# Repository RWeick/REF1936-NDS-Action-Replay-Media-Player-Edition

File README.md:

# REF1936-NDS-Action-Replay-Media-Player-Edition
The flash dump, schematic, and gerbers for the Datel Nintendo DS Action Replay Media Player edition. This is the version of the NDS Action Replay that has a functional micro SD card slot on it.

PCB Thickness: 0.8 mm

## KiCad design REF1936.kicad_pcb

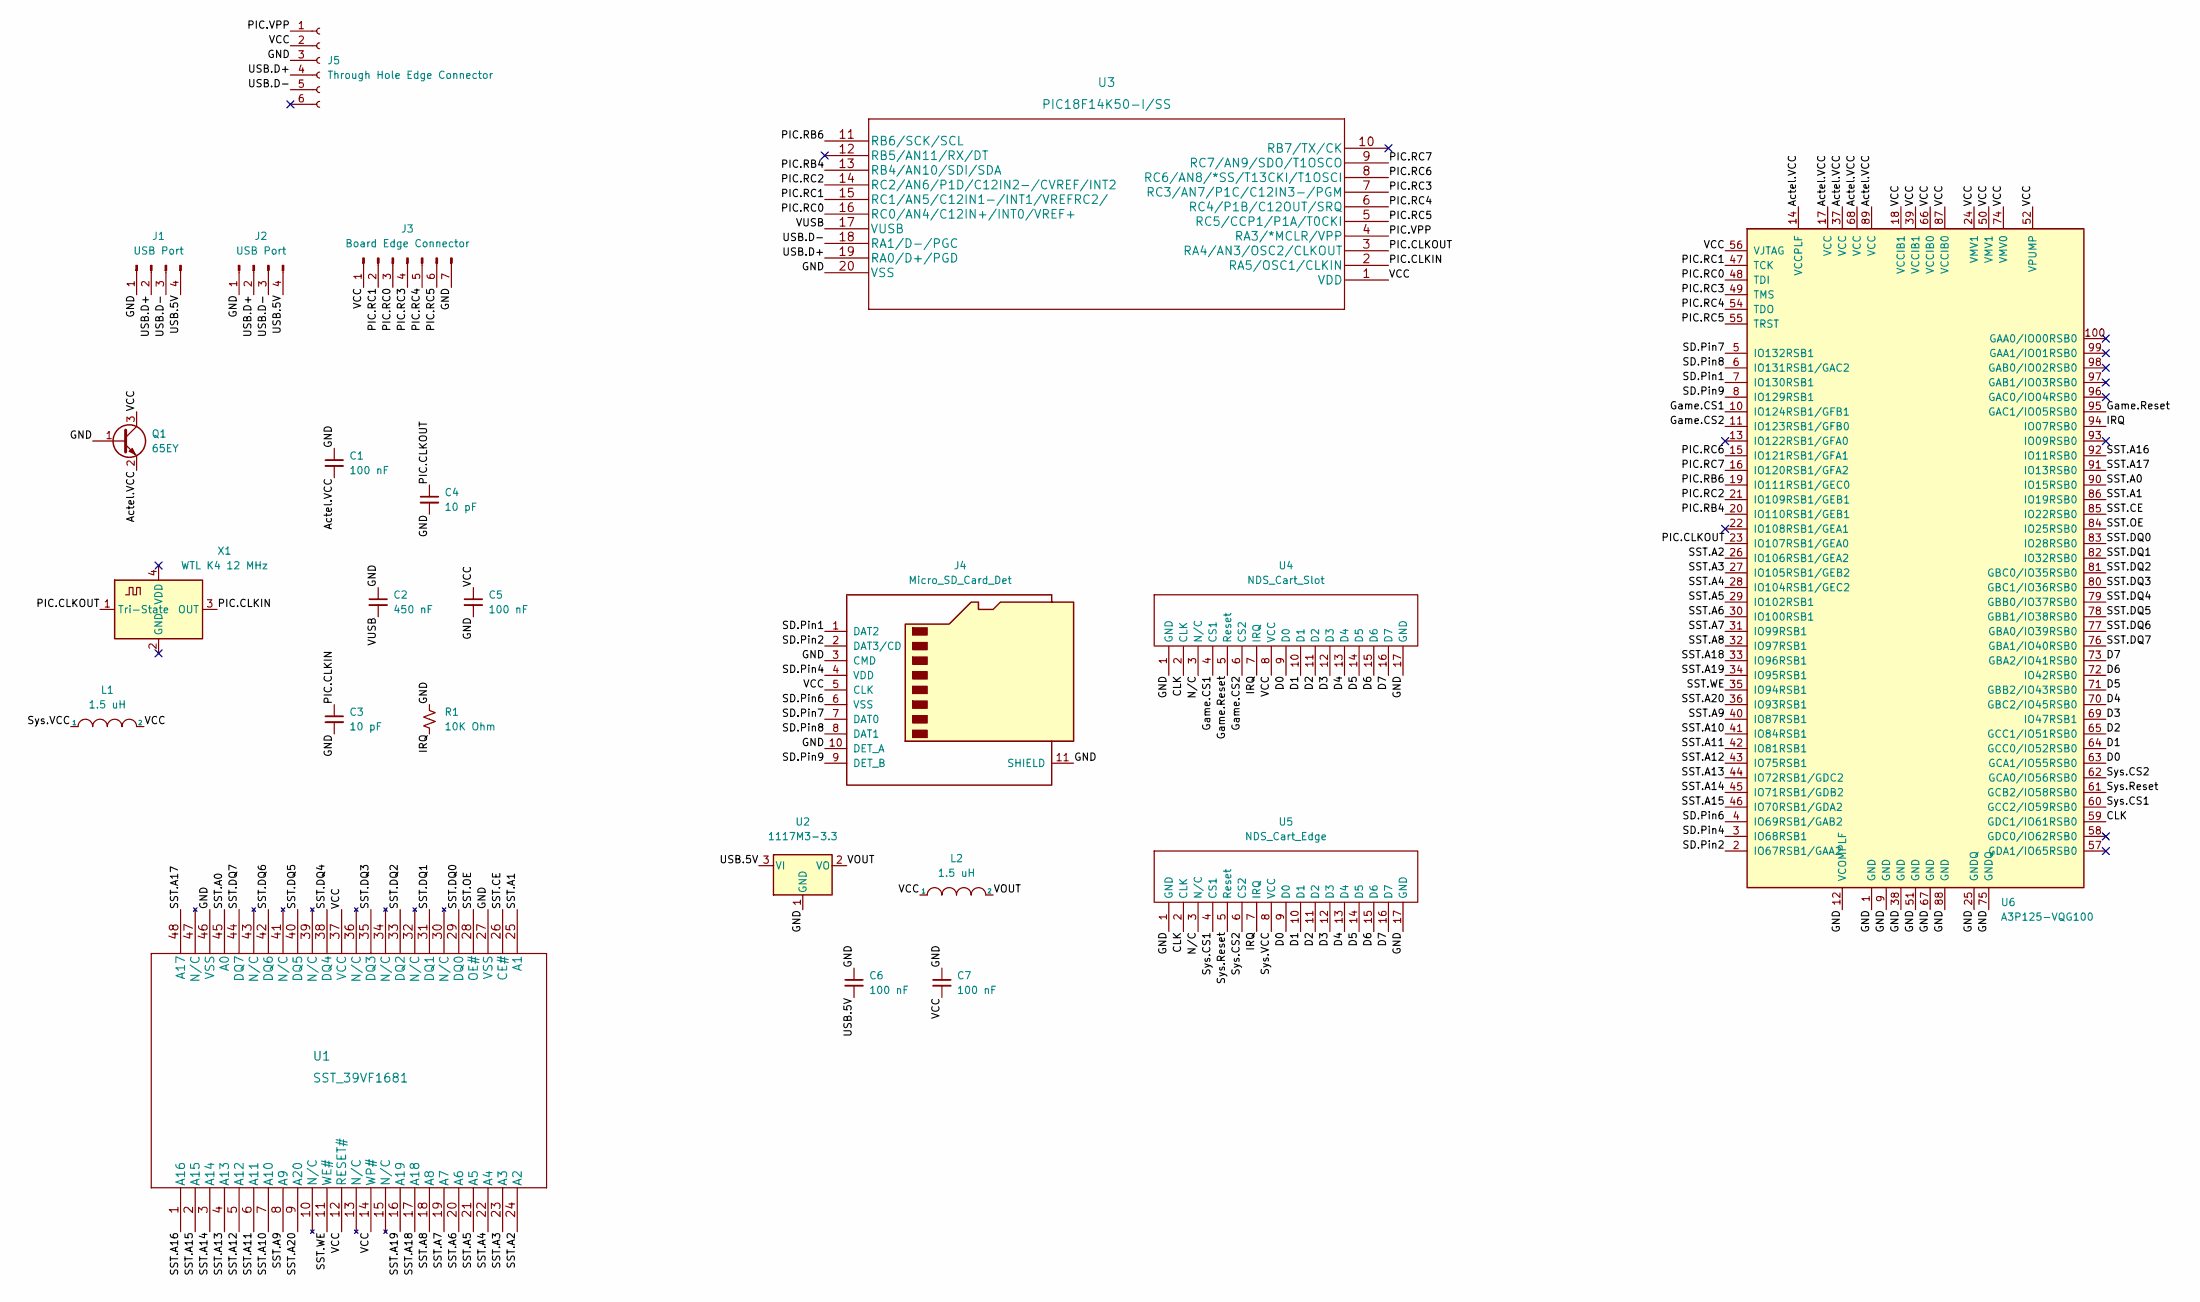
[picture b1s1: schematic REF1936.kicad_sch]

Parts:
C1, C5, C6, C7: 100 nF; Little SMD
C2: 450 nF; Little SMD
C3, C4: 10 pF; Little SMD
J1, J2: USB Port; USB Adapter
J3: Board Edge Connector; Board Edge Rear Connector
J4: Micro_SD_Card_Det; Micro SD Card
J5: Through Hole Edge Connector; PIC Edge Connector
L1, L2: 1.5 uH; Ferrite Inductor
Q1: 65EY; 65E9 SOT-23
R1: 10K Ohm; Little SMD
U1: SST_39VF1681; SOP50P2000X120-48N
U2: 1117M3-3.3; SOT229P700X180-4N
U3: PIC18F14K50-I/SS; PIC18F14K50-I&slash_SS
U4: NDS_Cart_Slot; DS Slot
U5: NDS_Cart_Edge; Edge Connector
U6: A3P125-VQG100; VQFP-100_14x14mm_P0.5mm
X1: WTL K4 12 MHz; Clock

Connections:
/Actel.VCC: C1.2, Q1.2 (E), U6.14 (VCCPLF), U6.17 (VCC), U6.37 (VCC), U6.68 (VCC), U6.89 (VCC)
/CLK: U4.2 (CLK), U5.2 (CLK), U6.59 (GDC1/IO61RSB0)
/D0: U4.9 (D0), U5.9 (D0), U6.63 (GCA1/IO55RSB0)
/D1: U4.10 (D1), U5.10 (D1), U6.64 (GCC0/IO52RSB0)
/D2: U4.11 (D2), U5.11 (D2), U6.65 (GCC1/IO51RSB0)
/D3: U4.12 (D3), U5.12 (D3), U6.69 (IO47RSB1)
/D4: U4.13 (D4), U5.13 (D4), U6.70 (GBC2/IO45RSB0)
/D5: U4.14 (D5), U5.14 (D5), U6.71 (GBB2/IO43RSB0)
/D6: U4.15 (D6), U5.15 (D6), U6.72 (IO42RSB0)
/D7: U4.16 (D7), U5.16 (D7), U6.73 (GBA2/IO41RSB0)
/GND: C1.1, C2.1, C3.2, C4.2, C5.2, C6.1, C7.1, J1.1, J2.1, J3.7, J4.3 (CMD), J4.10 (DET_A), J4.11 (SHIELD), J5.3, Q1.1 (B), R1.1, U1.27 (VSS), U1.46 (VSS), U2.1 (GND), U3.20 (VSS), U4.1 (GND), U4.17 (GND), U5.1 (GND), U5.17 (GND), U6.1 (GND), U6.9 (GND), U6.12 (VCOMPLF), U6.25 (GNDQ), U6.38 (GND), U6.51 (GND), U6.67 (GND), U6.75 (GNDQ), U6.88 (GND)
/Game.CS1: U4.4 (CS1), U6.10 (IO124RSB1/GFB1)
/Game.CS2: U4.6 (CS2), U6.11 (IO123RSB1/GFB0)
/Game.Reset: U4.5 (Reset), U6.95 (GAC1/IO05RSB0)
/IRQ: R1.2, U4.7 (IRQ), U5.7 (IRQ), U6.94 (IO07RSB0)
/N/C: U4.3 (N/C), U5.3 (N/C)
/PIC.CLKIN: C3.1, U3.2 (RA5/OSC1/CLKIN), X1.3 (OUT)
/PIC.CLKOUT: C4.1, U3.3 (RA4/AN3/OSC2/CLKOUT), U6.23 (IO107RSB1/GEA0), X1.1 (Tri-State)
/PIC.RB4: U3.13 (RB4/AN10/SDI/SDA), U6.20 (IO110RSB1/GEB1)
/PIC.RB6: U3.11 (RB6/SCK/SCL), U6.19 (IO111RSB1/GEC0)
/PIC.RC0: J3.3, U3.16 (RC0/AN4/C12IN+/INT0/VREF+), U6.48 (TDI)
/PIC.RC1: J3.2, U3.15 (RC1/AN5/C12IN1-/INT1/VREFRC2/), U6.47 (TCK)
/PIC.RC2: U3.14 (RC2/AN6/P1D/C12IN2-/CVREF/INT2), U6.21 (IO109RSB1/GEB1)
/PIC.RC3: J3.4, U3.7 (RC3/AN7/P1C/C12IN3-/PGM), U6.49 (TMS)
/PIC.RC4: J3.5, U3.6 (RC4/P1B/C12OUT/SRQ), U6.54 (TDO)
/PIC.RC5: J3.6, U3.5 (RC5/CCP1/P1A/T0CKI), U6.55 (TRST)
/PIC.RC6: U3.8 (RC6/AN8/*SS/T13CKI/T1OSCI), U6.15 (IO121RSB1/GFA1)
/PIC.RC7: U3.9 (RC7/AN9/SDO/T1OSCO), U6.16 (IO120RSB1/GFA2)
/PIC.VPP: J5.1, U3.4 (RA3/*MCLR/VPP)
/SD.Pin1: J4.1 (DAT2), U6.7 (IO130RSB1)
/SD.Pin2: J4.2 (DAT3/CD), U6.2 (IO67RSB1/GAA2)
/SD.Pin4: J4.4 (VDD), U6.3 (IO68RSB1)
/SD.Pin6: J4.6 (VSS), U6.4 (IO69RSB1/GAB2)
/SD.Pin7: J4.7 (DAT0), U6.5 (IO132RSB1)
/SD.Pin8: J4.8 (DAT1), U6.6 (IO131RSB1/GAC2)
/SD.Pin9: J4.9 (DET_B), U6.8 (IO129RSB1)
/SST.A0: U1.45 (A0), U6.90 (IO15RSB0)
/SST.A1: U1.25 (A1), U6.86 (IO19RSB0)
/SST.A2: U1.24 (A2), U6.26 (IO106RSB1/GEA2)
/SST.A3: U1.23 (A3), U6.27 (IO105RSB1/GEB2)
/SST.A4: U1.22 (A4), U6.28 (IO104RSB1/GEC2)
/SST.A5: U1.21 (A5), U6.29 (IO102RSB1)
/SST.A6: U1.20 (A6), U6.30 (IO100RSB1)
/SST.A7: U1.19 (A7), U6.31 (IO99RSB1)
/SST.A8: U1.18 (A8), U6.32 (IO97RSB1)
/SST.A9: U1.8 (A9), U6.40 (IO87RSB1)
/SST.A10: U1.7 (A10), U6.41 (IO84RSB1)
/SST.A11: U1.6 (A11), U6.42 (IO81RSB1)
/SST.A12: U1.5 (A12), U6.43 (IO75RSB1)
/SST.A13: U1.4 (A13), U6.44 (IO72RSB1/GDC2)
/SST.A14: U1.3 (A14), U6.45 (IO71RSB1/GDB2)
/SST.A15: U1.2 (A15), U6.46 (IO70RSB1/GDA2)
/SST.A16: U1.1 (A16), U6.92 (IO11RSB0)
/SST.A17: U1.48 (A17), U6.91 (IO13RSB0)
/SST.A18: U1.17 (A18), U6.33 (IO96RSB1)
/SST.A19: U1.16 (A19), U6.34 (IO95RSB1)
/SST.A20: U1.9 (A20), U6.36 (IO93RSB1)
/SST.CE: U1.26 (CE#), U6.85 (IO22RSB0)
/SST.DQ0: U1.29 (DQ0), U6.83 (IO28RSB0)
/SST.DQ1: U1.31 (DQ1), U6.82 (IO32RSB0)
/SST.DQ2: U1.33 (DQ2), U6.81 (GBC0/IO35RSB0)
/SST.DQ3: U1.35 (DQ3), U6.80 (GBC1/IO36RSB0)
/SST.DQ4: U1.38 (DQ4), U6.79 (GBB0/IO37RSB0)
/SST.DQ5: U1.40 (DQ5), U6.78 (GBB1/IO38RSB0)
/SST.DQ6: U1.42 (DQ6), U6.77 (GBA0/IO39RSB0)
/SST.DQ7: U1.44 (DQ7), U6.76 (GBA1/IO40RSB0)
/SST.OE: U1.28 (OE#), U6.84 (IO25RSB0)
/SST.WE: U1.11 (WE#), U6.35 (IO94RSB1)
/Sys.CS1: U5.4 (CS1), U6.60 (GCC2/IO59RSB0)
/Sys.CS2: U5.6 (CS2), U6.62 (GCA0/IO56RSB0)
/Sys.Reset: U5.5 (Reset), U6.61 (GCB2/IO58RSB0)
/Sys.VCC: L1.1, U5.8 (VCC)
/USB.5V: C6.2, J1.4, J2.4, U2.3 (VI)
/USB.D+: J1.2, J2.2, J5.4, U3.19 (RA0/D+/PGD)
/USB.D-: J1.3, J2.3, J5.5, U3.18 (RA1/D-/PGC)
/VCC: C5.1, C7.2, J3.1, J4.5 (CLK), J5.2, L1.2, L2.1, Q1.3 (C), U1.12 (RESET#), U1.14 (WP#), U1.37 (VCC), U3.1 (VDD), U4.8 (VCC), U6.18 (VCCIB1), U6.24 (VMV1), U6.39 (VCCIB1), U6.50 (VMV1), U6.52 (VPUMP), U6.56 (VJTAG), U6.66 (VCCIB0), U6.74 (VMV0), U6.87 (VCCIB0)
/VOUT: L2.2, U2.2 (VO)
/VUSB: C2.2, U3.17 (VUSB)

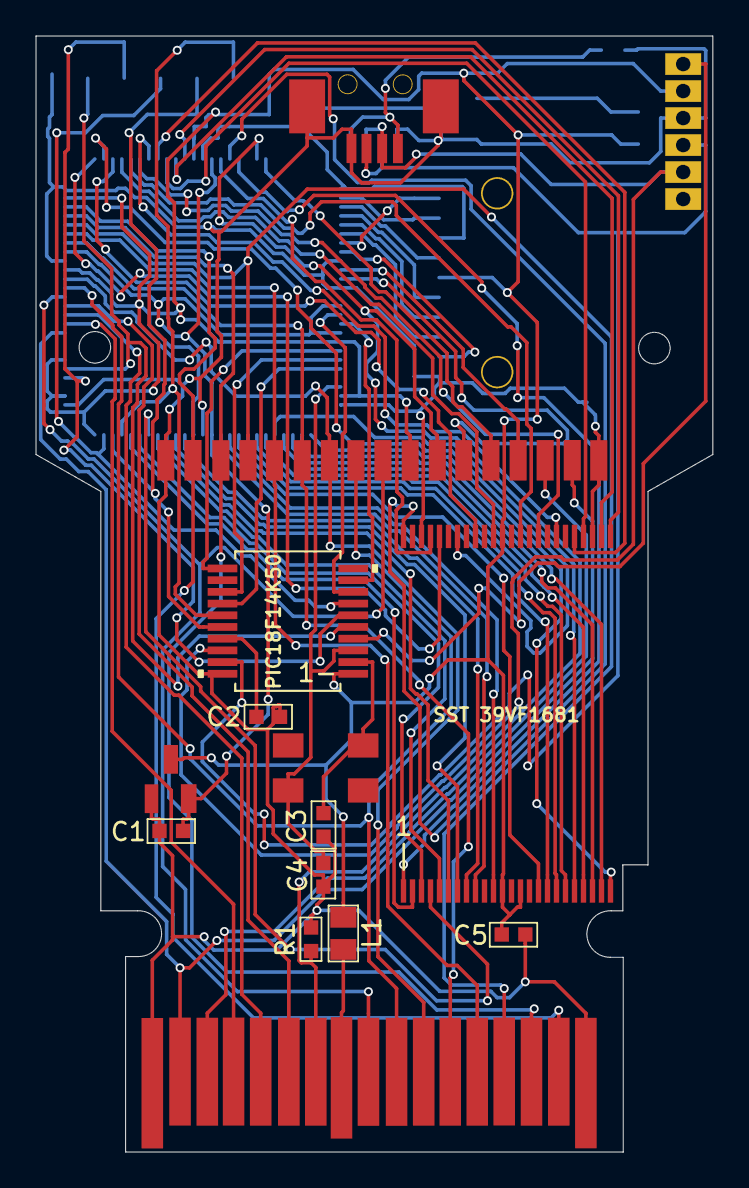
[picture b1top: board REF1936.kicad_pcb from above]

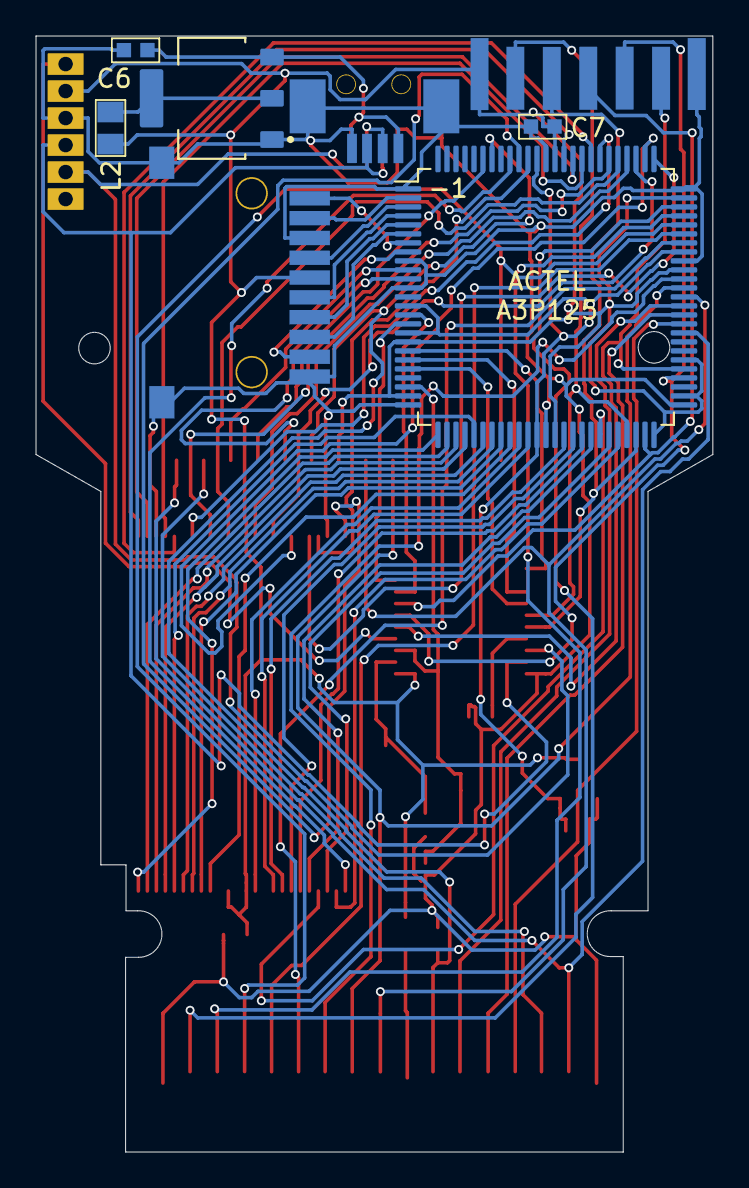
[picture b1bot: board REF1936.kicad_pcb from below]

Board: 2 copper layers, 37.6 x 62.0 mm, 25 parts (6 on the bottom side), 78 nets.

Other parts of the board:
H1, H2: MountingHole_2.1mm

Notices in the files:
parts and their libraries:
Copyright 2021 Accelerated Designs. All rights reserved.
